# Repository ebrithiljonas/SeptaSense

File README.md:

# Septa Sense

Septa Sense in an Open Source and Open Hardware IoT air quality sensor, based on an ESP32 running ESPHome. It features a rim of RGB-LEDs around the top which indicate the quality of the air. Measurements can be seen either on in the integrated display or over Home Assistant. The unit is powered with a USB-C plug on the backside.

## Capabilities
- Temperature (0 - 50°C ± 0.5°C)
- Humidity (0 - 100% ± 4.5%)
- VOC (1 - 500 Index ± 5 Index)
- NOx (1 - 500 Index ± 10 Index)
- Particulate Matter (0 - 1000 μg/m³ ± 10%)
- CO2 (400 - 5000 ppm ± (40 ppm + 5%))
- Pressure (300 - 1250 hPa ± 0.5 hPa)

### Sensors
- [SEN55](https://sensirion.com/products/catalog/SEN55/)
- [SCD41](https://sensirion.com/products/catalog/SCD41/)
- [BMP388](https://www.bosch-sensortec.com/products/environmental-sensors/pressure-sensors/bmp388/)

## Mainboard

The mainboard is a custom PCB which holds the ESP32 chip, the BMP388 and SCD41 sensors and the RGB LEDs. The SEN55 sensor and the display are connected to it with a cable that is directly soldered to the board. It gets power via the USB-C plug over a cable with a JST XH connector that is mounted on the PCB.

## 3D-Print

The case consists of 5 different 3D printed parts. Recommended print settings are:

- Case Bottom
  - Layer height: 0.2 mm
  - Infill: 10 %
  - Support: Yes
  - Support overhang: 80°
- Case Top
  - Layer height: 0.2 mm
  - Infill: 10 %
  - Support: No
- LED Ring
  - Layer height: 0.2 mm
  - Infill: 20 %
  - Support: No
- SEN55 Bracket
  - Layer height: 0.1 mm
  - Infill: 20 %
  - Support: No
- Display Fixture
  - Layer height: 0.2 mm
  - Infill: 20 %
  - Support: No

## BOM
- 1x [Mainboard](#mainboard)
- 1x [SEN55](https://sensirion.com/products/catalog/SEN55/)
- 1x [SCD41](https://sensirion.com/products/catalog/SCD41/)
- 1x Display [SD1306 128x64](https://www.aliexpress.com/item/32638662748.html)
- 1x [USB-C Connector](https://www.aliexpress.com/item/1005001714874457.html)
- 1x Micro JST GH 6 pin Cable
- 1x JST XH 2 Pin Cable
- 1x Dupont Female 4 pin Cable
- 2x M3x5,7-OD 4,6 heat inserts
- 2x M3x10 countersunk screws
- 1x [Set of 3D-Prints](#3d-print)

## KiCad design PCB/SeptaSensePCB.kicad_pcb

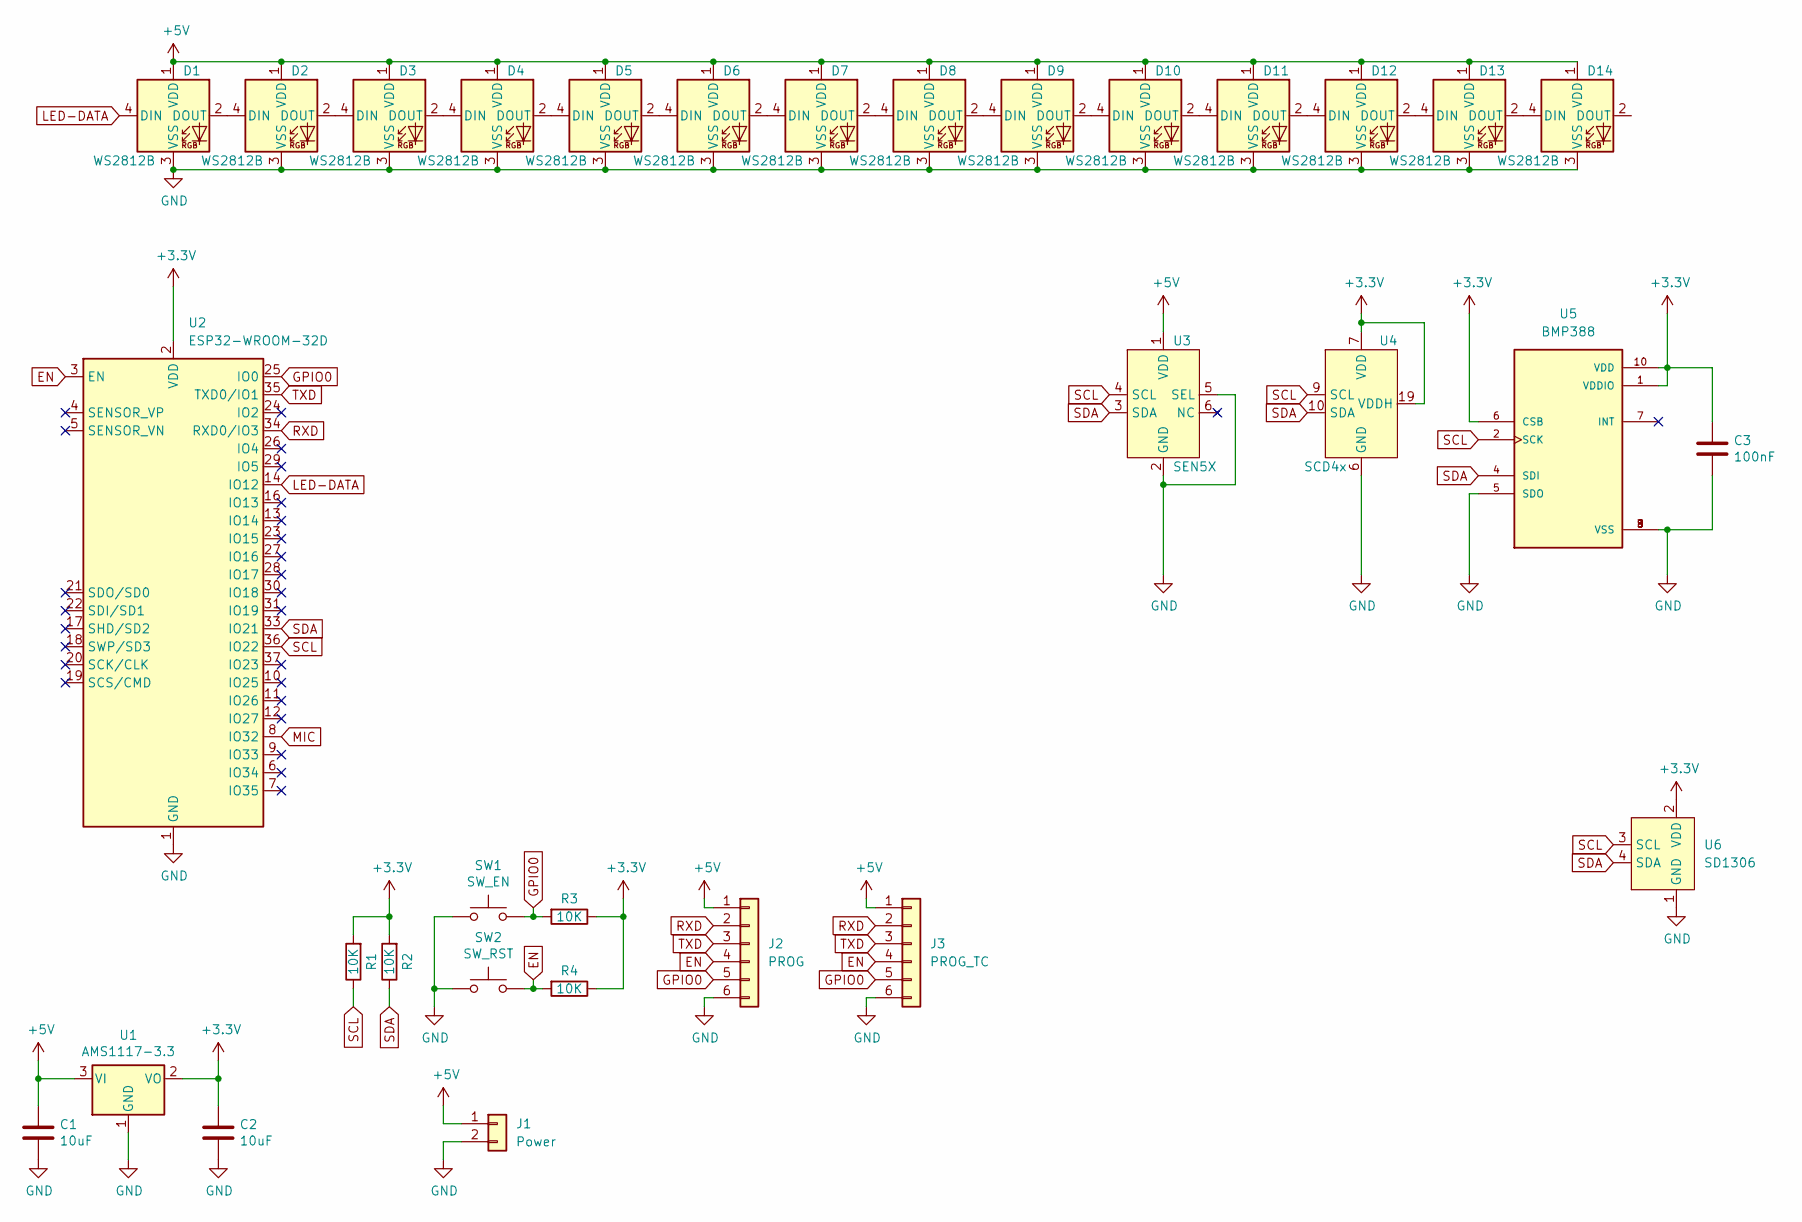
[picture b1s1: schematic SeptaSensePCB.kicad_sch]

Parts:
C1, C2: 10uF; C_0805_2012Metric_Pad1.18x1.45mm_HandSolder; LCSC C17024
C3: 100nF; C_0805_2012Metric_Pad1.18x1.45mm_HandSolder; LCSC C1711
D1, D2, D3, D4, D5, D6, D7, D8, D9, D10, D11, D12, D13, D14: WS2812B; LED_WS2812B_PLCC4_5.0x5.0mm_P3.2mm; JLC SMD,5x5mm
J1: Power; JST_XH_B2B-XH-A_1x02_P2.50mm_Vertical
J2: PROG; PinHeader_1x06_P2.54mm_Vertical
J3: PROG_TC; Tag-Connect_TC2030-IDC-FP_2x03_P1.27mm_Vertical
R1, R2, R3, R4: 10K; C_0805_2012Metric_Pad1.18x1.45mm_HandSolder; JLC 0805
SW1: SW_EN; SW_SPST_CK_RS282G05A3; JLC KEY-SMD
SW2: SW_RST; SW_SPST_CK_RS282G05A3; JLC KEY-SMD
U1: AMS1117-3.3; SOT-223-3_TabPin2; JLC SOT-223
U2: ESP32-WROOM-32D; ESP32-WROOM-32; LCSC C473012
U3: SEN5X; PinHeader_1x06_P2.54mm_Vertical
U4: SCD4x; Sensirion_SCD4x_10.1x10.x_P1.0mm
U5: BMP388; PQFN50P200X200X80-10N; PARTREV 1.1; LCSC C779278
U6: SD1306; PinHeader_1x04_P2.54mm_Vertical

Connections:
+3V3: C2.1, C3.1, R1.2, R2.2, R3.1, R4.1, U1.2 (VO), U2.2 (VDD), U4.7 (VDD), U4.19 (VDDH), U5.1 (VDDIO), U5.6 (CSB), U5.10 (VDD), U6.2 (VDD)
+5V: C1.1, D1.1 (VDD), D2.1 (VDD), D3.1 (VDD), D4.1 (VDD), D5.1 (VDD), D6.1 (VDD), D7.1 (VDD), D8.1 (VDD), D9.1 (VDD), D10.1 (VDD), D11.1 (VDD), D12.1 (VDD), D13.1 (VDD), D14.1 (VDD), J1.1, J2.1, J3.1, U1.3 (VI), U3.1 (VDD)
EN: J2.4, J3.4, R4.2, SW2.2, U2.3 (EN)
GND: C1.2, C2.2, C3.2, D1.3 (VSS), D2.3 (VSS), D3.3 (VSS), D4.3 (VSS), D5.3 (VSS), D6.3 (VSS), D7.3 (VSS), D8.3 (VSS), D9.3 (VSS), D10.3 (VSS), D11.3 (VSS), D12.3 (VSS), D13.3 (VSS), D14.3 (VSS), J1.2, J2.6, J3.6, SW1.1, SW2.1, U1.1 (GND), U2.1 (GND), U2.15 (GND), U2.38 (GND), U2.39 (GND), U3.2 (GND), U3.5 (SEL), U4.6 (GND), U4.20 (GND), U4.21 (GND), U5.3 (VSS), U5.5 (SDO), U5.8 (VSS), U5.9 (VSS), U6.1 (GND)
GPIO0: J2.5, J3.5, R3.2, SW1.2, U2.25 (IO0)
LED-DATA: D1.4 (DIN), U2.14 (IO12)
MIC: U2.8 (IO32)
unnamed: D1.2 (DOUT), D2.4 (DIN)
unnamed: D2.2 (DOUT), D3.4 (DIN)
unnamed: D3.2 (DOUT), D4.4 (DIN)
unnamed: D4.2 (DOUT), D5.4 (DIN)
unnamed: D5.2 (DOUT), D6.4 (DIN)
unnamed: D6.2 (DOUT), D7.4 (DIN)
unnamed: D7.2 (DOUT), D8.4 (DIN)
unnamed: D8.2 (DOUT), D9.4 (DIN)
unnamed: D10.2 (DOUT), D11.4 (DIN)
unnamed: D9.2 (DOUT), D10.4 (DIN)
unnamed: D11.2 (DOUT), D12.4 (DIN)
unnamed: D12.2 (DOUT), D13.4 (DIN)
unnamed: D13.2 (DOUT), D14.4 (DIN)
RXD: J2.2, J3.2, U2.34 (RXD0/IO3)
SCL: R1.1, U2.36 (IO22), U3.4 (SCL), U4.9 (SCL), U5.2 (SCK), U6.3 (SCL)
SDA: R2.1, U2.33 (IO21), U3.3 (SDA), U4.10 (SDA), U5.4 (SDI), U6.4 (SDA)
TXD: J2.3, J3.3, U2.35 (TXD0/IO1)

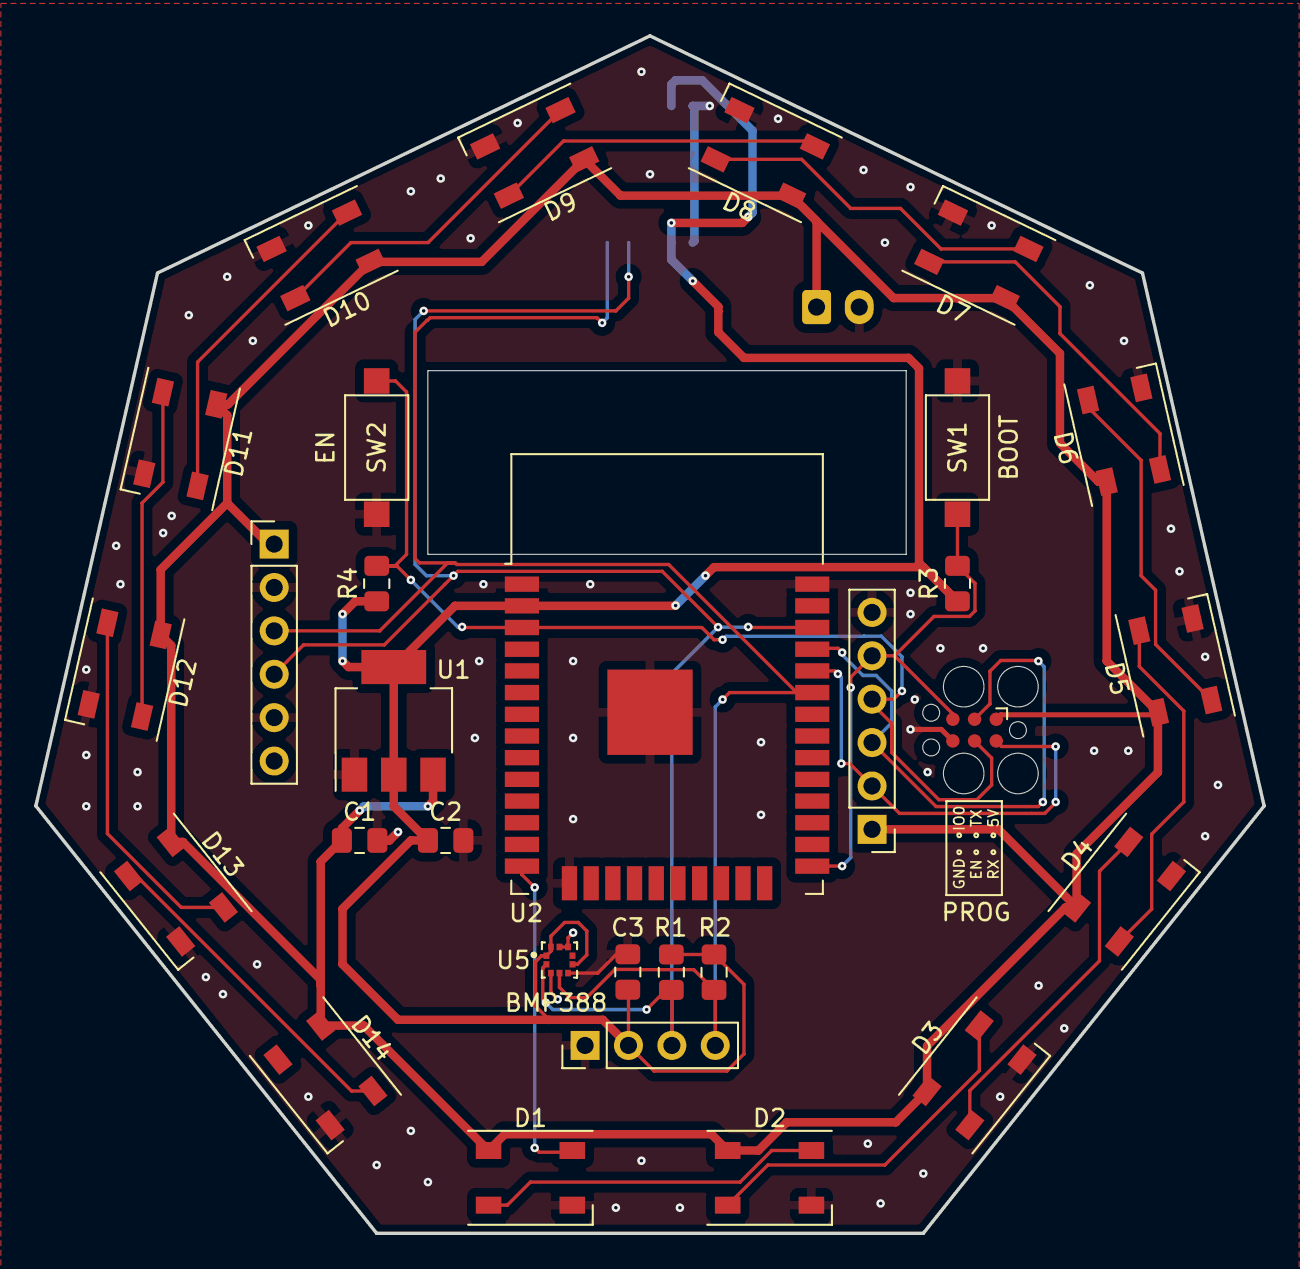
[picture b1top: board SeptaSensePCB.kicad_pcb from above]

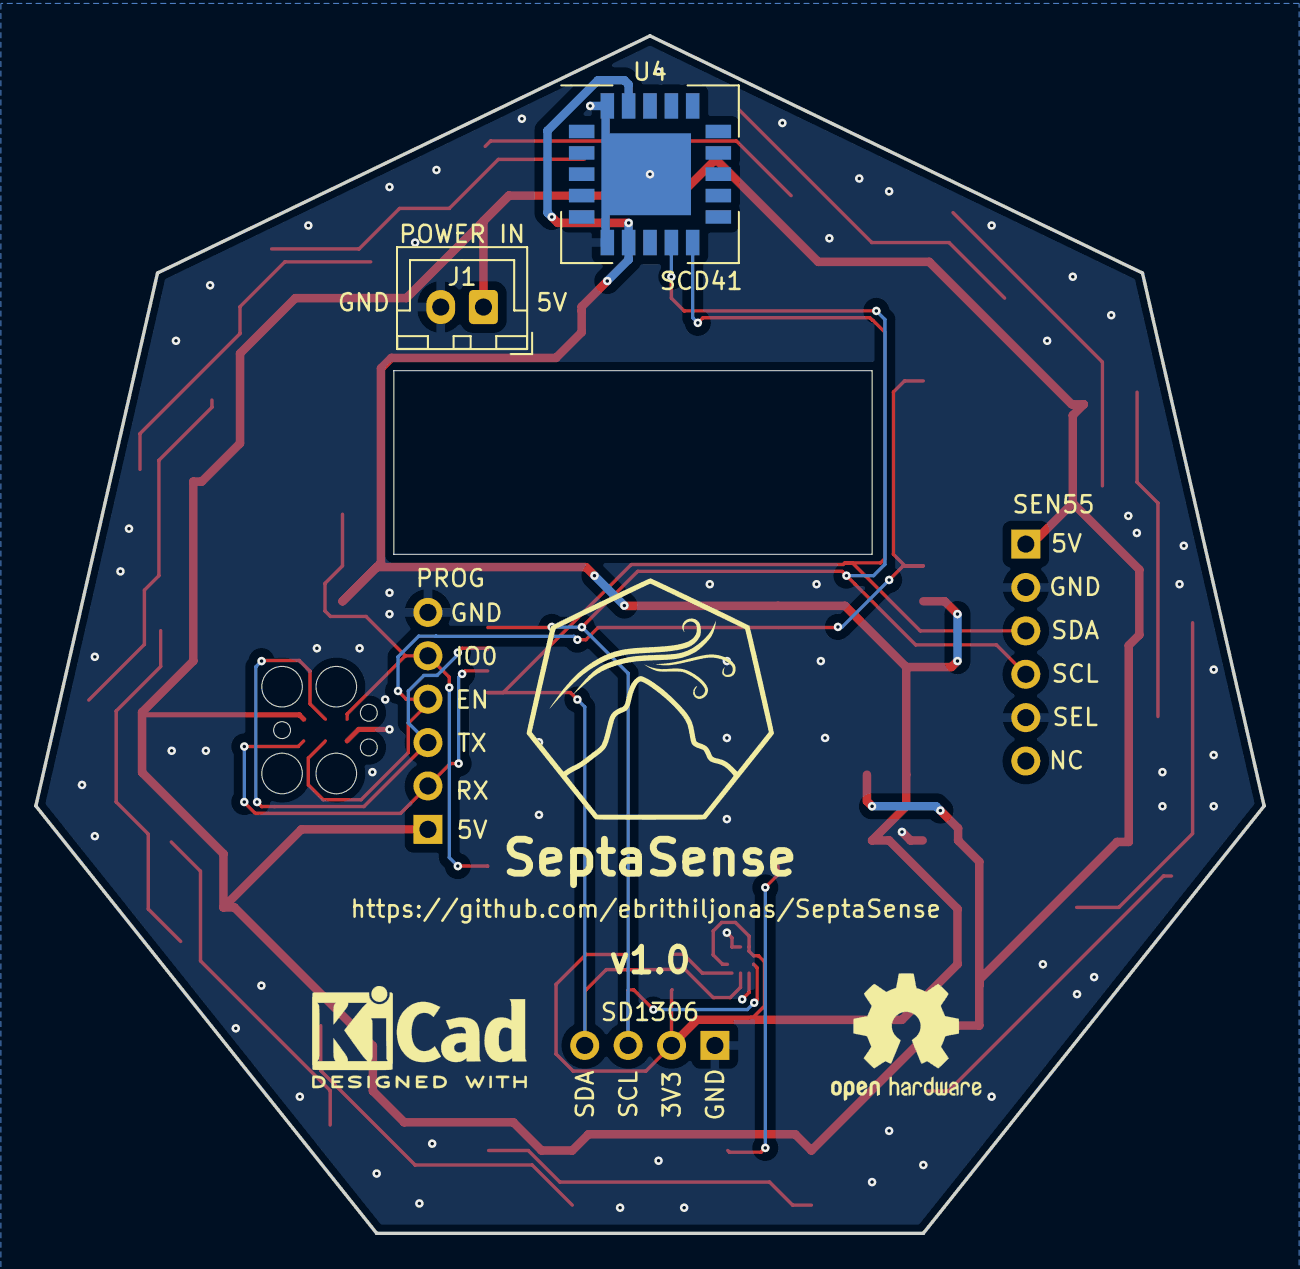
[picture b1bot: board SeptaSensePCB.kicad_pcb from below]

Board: 2 copper layers, 71.9 x 70.1 mm, 32 parts (2 on the bottom side), 23 nets.

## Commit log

2022-11-05 Firmware Small Changes
